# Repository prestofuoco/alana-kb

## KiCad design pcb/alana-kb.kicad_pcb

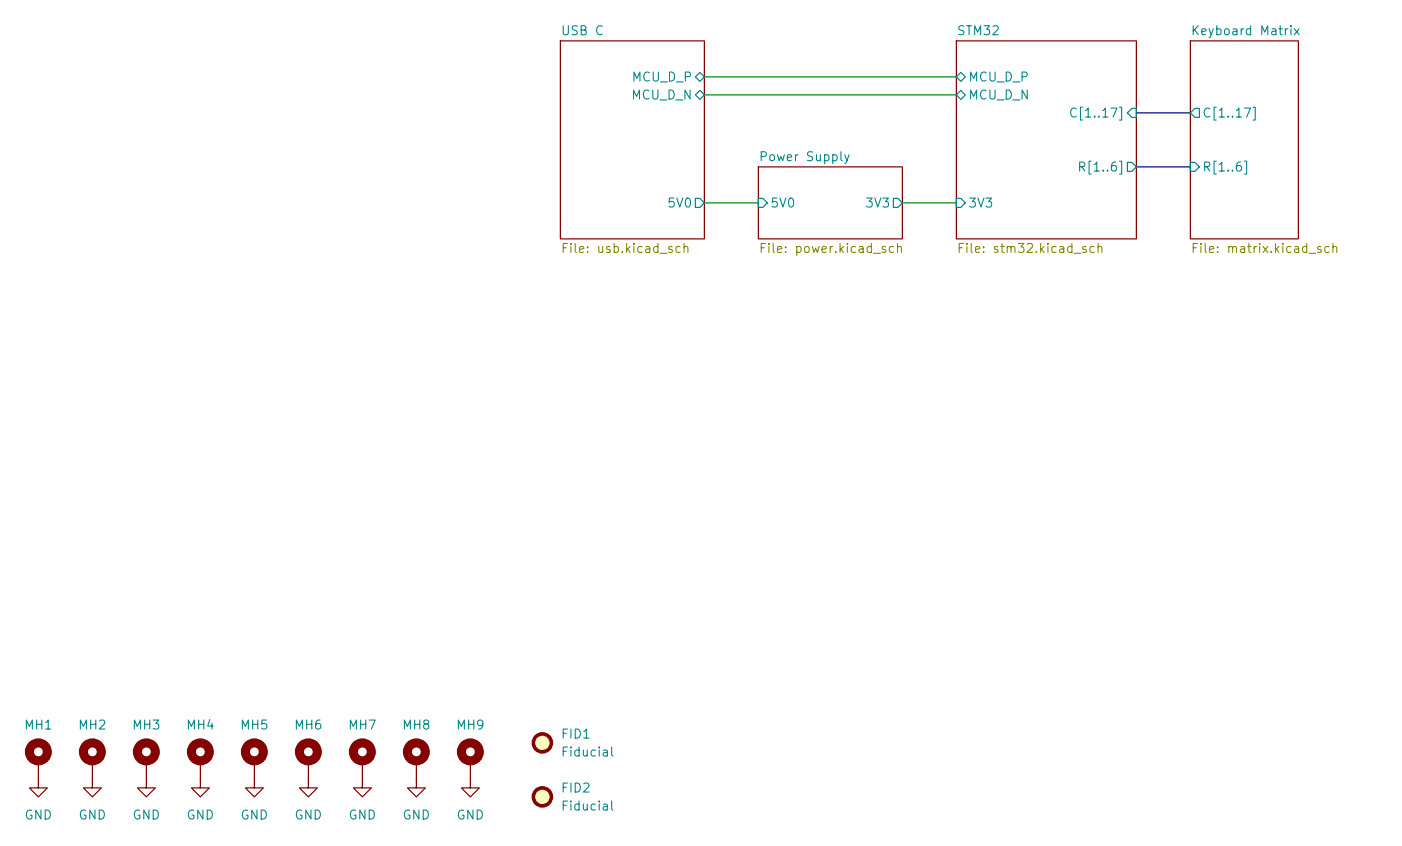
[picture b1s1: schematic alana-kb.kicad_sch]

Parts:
FID1, FID2: Fiducial; Fiducial_1.5mm_Mask4.5mm
MH1, MH2, MH3, MH4, MH5, MH6, MH7, MH8, MH9: MountingHole_Pad; MountingHole_2.2mm_M2_ISO7380_Pad

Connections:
GND: MH1.1, MH2.1, MH3.1, MH4.1, MH5.1, MH6.1, MH7.1, MH8.1, MH9.1; also elsewhere on the board

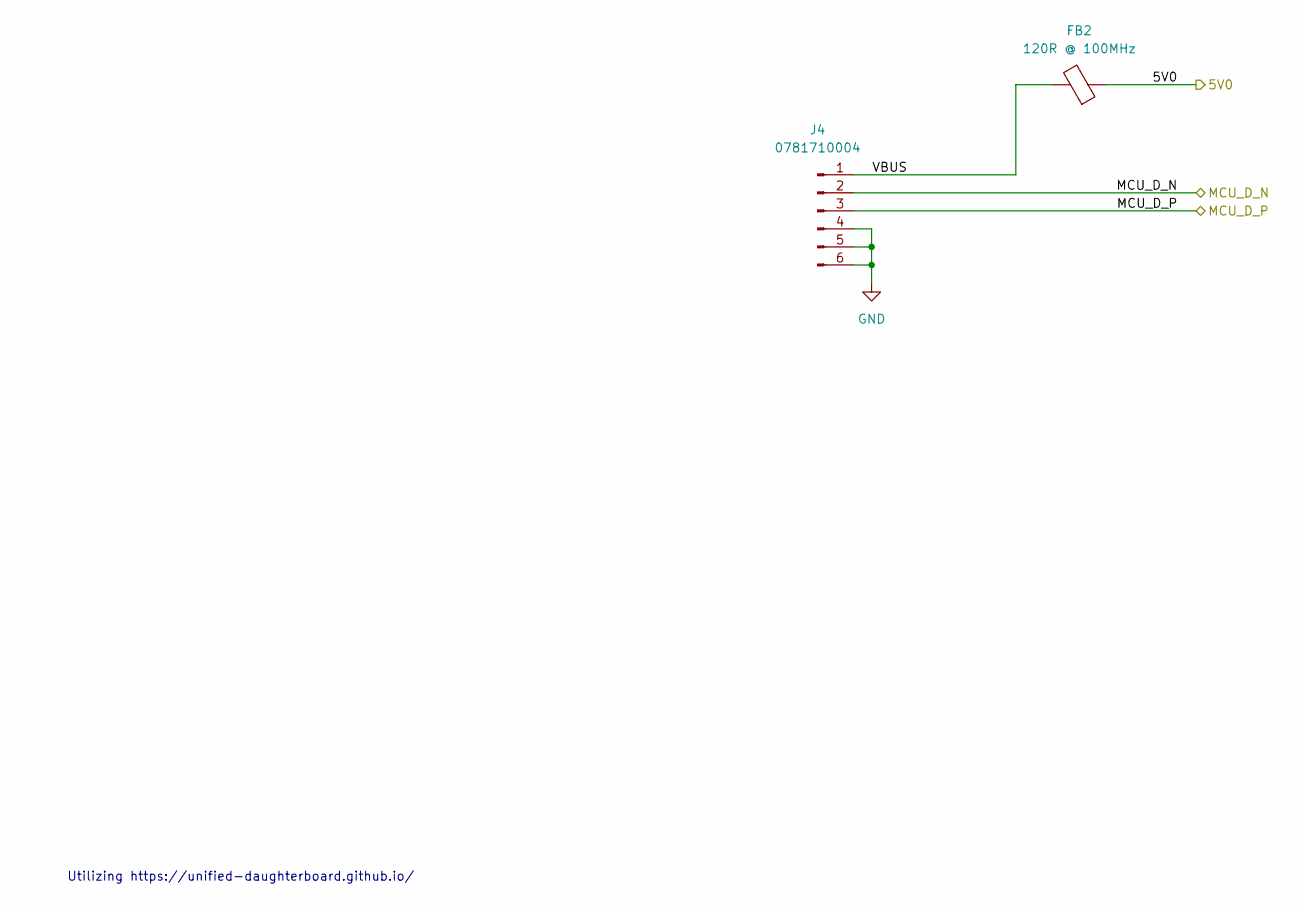
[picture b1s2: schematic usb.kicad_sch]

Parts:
FB2: 120R @ 100MHz; L_0805_2012Metric
J4: 0781710004; CONN_781710000-SD_04_MOL

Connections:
/Power Supply/5V0: FB2.1; also elsewhere on the board
/STM32/MCU_D_N: J4.2; also elsewhere on the board
/STM32/MCU_D_P: J4.3; also elsewhere on the board
/USB C/VBUS: FB2.2, J4.1
GND: J4.4, J4.5, J4.6; also elsewhere on the board

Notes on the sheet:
Utilizing https://unified-daughterboard.github.io/

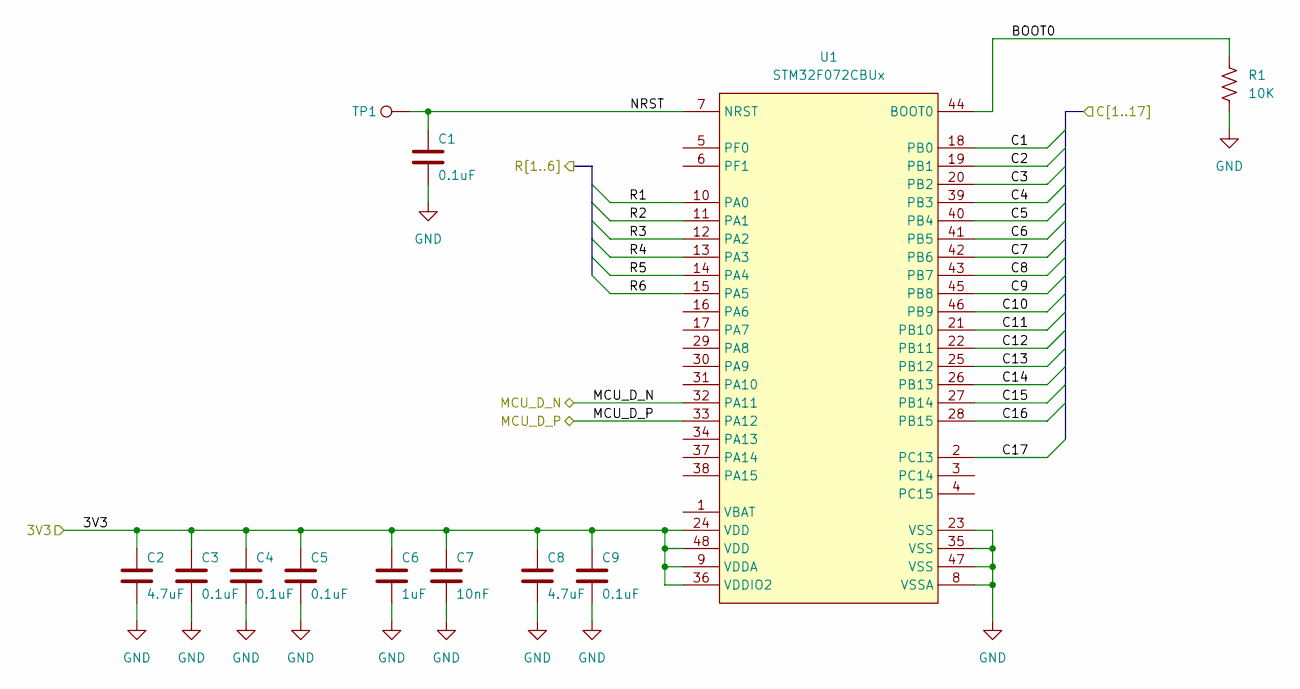
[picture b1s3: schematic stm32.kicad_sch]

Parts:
C1, C3, C4, C5, C9: 0.1uF; C_0402_1005Metric
C2, C8: 4.7uF; C_0603_1608Metric
C6: 1uF; C_0402_1005Metric
C7: 10nF; C_0402_1005Metric
R1: 10K; R_0402_1005Metric
TP1: TestPoint; TestPoint_Pad_D1.0mm
U1: STM32F072CBUx; QFN-48-1EP_7x7mm_P0.5mm_EP5.6x5.6mm

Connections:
/Keyboard Matrix/C1: U1.18 (PB0); also elsewhere on the board
/Keyboard Matrix/C2: U1.19 (PB1); also elsewhere on the board
/Keyboard Matrix/C3: U1.20 (PB2); also elsewhere on the board
/Keyboard Matrix/C4: U1.39 (PB3); also elsewhere on the board
/Keyboard Matrix/C5: U1.40 (PB4); also elsewhere on the board
/Keyboard Matrix/C6: U1.41 (PB5); also elsewhere on the board
/Keyboard Matrix/C7: U1.42 (PB6); also elsewhere on the board
/Keyboard Matrix/C8: U1.43 (PB7); also elsewhere on the board
/Keyboard Matrix/C9: U1.45 (PB8); also elsewhere on the board
/Keyboard Matrix/C10: U1.46 (PB9); also elsewhere on the board
/Keyboard Matrix/C11: U1.21 (PB10); also elsewhere on the board
/Keyboard Matrix/C12: U1.22 (PB11); also elsewhere on the board
/Keyboard Matrix/C13: U1.25 (PB12); also elsewhere on the board
/Keyboard Matrix/C14: U1.26 (PB13); also elsewhere on the board
/Keyboard Matrix/C15: U1.27 (PB14); also elsewhere on the board
/Keyboard Matrix/C16: U1.28 (PB15); also elsewhere on the board
/Keyboard Matrix/C17: U1.2 (PC13); also elsewhere on the board
/Keyboard Matrix/R1: U1.10 (PA0); also elsewhere on the board
/Keyboard Matrix/R2: U1.11 (PA1); also elsewhere on the board
/Keyboard Matrix/R3: U1.12 (PA2); also elsewhere on the board
/Keyboard Matrix/R4: U1.13 (PA3); also elsewhere on the board
/Keyboard Matrix/R5: U1.14 (PA4); also elsewhere on the board
/Keyboard Matrix/R6: U1.15 (PA5); also elsewhere on the board
/Power Supply/3V3: C2.1, C3.1, C4.1, C5.1, C6.1, C7.1, C8.1, C9.1, U1.9 (VDDA), U1.24 (VDD), U1.36 (VDDIO2), U1.48 (VDD); also elsewhere on the board
/STM32/BOOT0: R1.1, U1.44 (BOOT0)
/STM32/MCU_D_N: U1.32 (PA11); also elsewhere on the board
/STM32/MCU_D_P: U1.33 (PA12); also elsewhere on the board
/STM32/NRST: C1.1, TP1.1, U1.7 (NRST)
GND: C1.2, C2.2, C3.2, C4.2, C5.2, C6.2, C7.2, C8.2, C9.2, R1.2, U1.8 (VSSA), U1.23 (VSS), U1.35 (VSS), U1.47 (VSS), U1.49 (GND); also elsewhere on the board

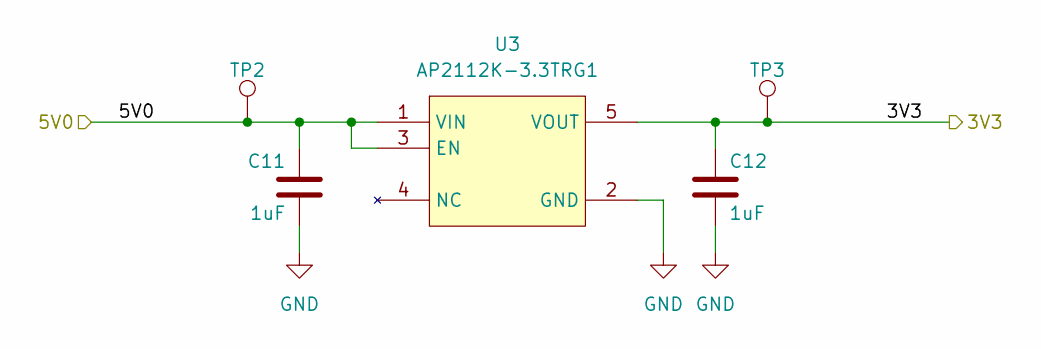
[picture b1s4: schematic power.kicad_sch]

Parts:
C11, C12: 1uF; C_0402_1005Metric
TP2, TP3: TestPoint; TestPoint_Pad_D2.0mm
U3: AP2112K-3.3TRG1; SOT-23-5

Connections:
/Power Supply/3V3: C12.1, TP3.1, U3.5 (VOUT); also elsewhere on the board
/Power Supply/5V0: C11.1, TP2.1, U3.1 (VIN), U3.3 (EN); also elsewhere on the board
GND: C11.2, C12.2, U3.2 (GND); also elsewhere on the board

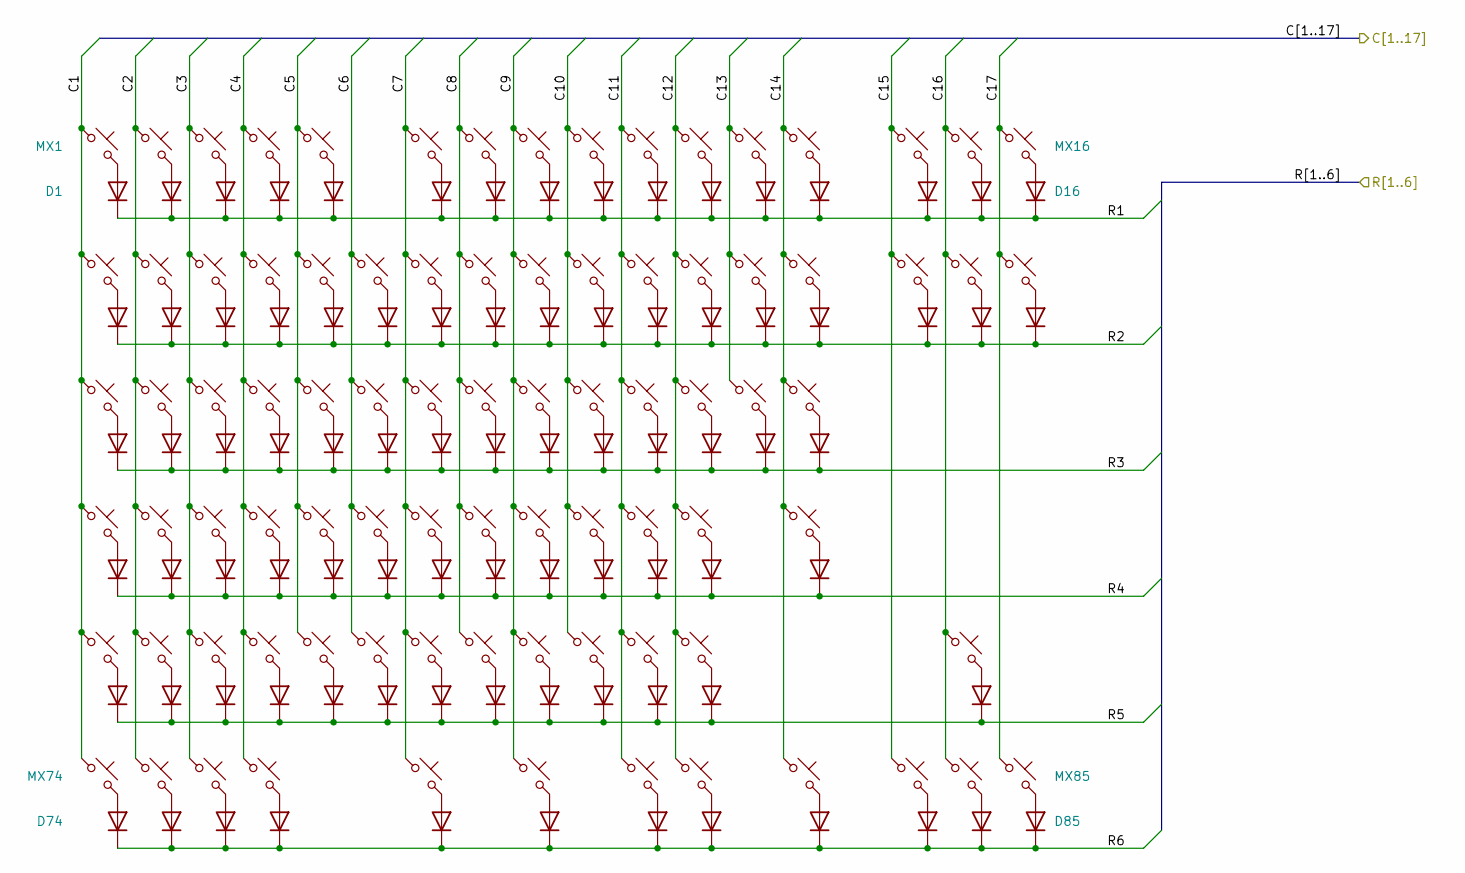
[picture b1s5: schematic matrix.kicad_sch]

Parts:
D1, D2, D3, D4, D5, D6, D7, D8, D9, D10, D11, D12, D13, D14, D15, D16, D17, D18, D19, D20, D21, D22, D23, D24, D25, D26, D27, D28, D29, D30, D31, D32, D33, D34, D35, D36, D37, D38, D39, D40, D41, D42, D43, D44, D45, D46, D47, D48, D49, D50, D51, D52, D53, D54, D55, D56, D57, D58, D59, D60, D61, D62, D63, D64, D65, D66, D67, D68, D69, D70, D71, D72, D73, D74, D75, D76, D77, D78, D79, D80, D81, D82, D83, D84, D85: 1N4148W; D_SOD-123
MX1, MX2, MX3, MX4, MX5, MX6, MX7, MX8, MX9, MX10, MX11, MX12, MX13, MX14, MX15, MX16, MX17, MX18, MX19, MX20, MX21, MX22, MX23, MX24, MX25, MX26, MX27, MX28, MX29, MX30, MX31, MX32, MX33, MX34, MX35, MX36, MX37, MX38, MX39, MX40, MX41, MX42, MX43, MX44, MX45, MX46, MX47, MX48, MX49, MX50, MX51, MX52, MX53, MX54, MX55, MX56, MX57, MX58, MX59, MX60, MX61, MX62, MX63, MX64, MX65, MX66, MX67, MX68, MX69, MX70, MX71, MX72, MX73, MX74, MX75, MX76, MX77, MX78, MX79, MX80, MX81, MX82, MX83, MX84, MX85: MX_SW_solder; SW_MX_1u

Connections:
/Keyboard Matrix/C1: MX1.1, MX17.1, MX34.1, MX48.1, MX61.1, MX74.1; also elsewhere on the board
/Keyboard Matrix/C2: MX2.1, MX18.1, MX35.1, MX49.1, MX62.1, MX75.1; also elsewhere on the board
/Keyboard Matrix/C3: MX3.1, MX19.1, MX36.1, MX50.1, MX63.1, MX76.1; also elsewhere on the board
/Keyboard Matrix/C4: MX4.1, MX20.1, MX37.1, MX51.1, MX64.1, MX77.1; also elsewhere on the board
/Keyboard Matrix/C5: MX5.1, MX21.1, MX38.1, MX52.1, MX65.1; also elsewhere on the board
/Keyboard Matrix/C6: MX22.1, MX39.1, MX53.1, MX66.1; also elsewhere on the board
/Keyboard Matrix/C7: MX6.1, MX23.1, MX40.1, MX54.1, MX67.1, MX78.1; also elsewhere on the board
/Keyboard Matrix/C8: MX7.1, MX24.1, MX41.1, MX55.1, MX68.1; also elsewhere on the board
/Keyboard Matrix/C9: MX8.1, MX25.1, MX42.1, MX56.1, MX69.1, MX79.1; also elsewhere on the board
/Keyboard Matrix/C10: MX9.1, MX26.1, MX43.1, MX57.1, MX70.1; also elsewhere on the board
/Keyboard Matrix/C11: MX10.1, MX27.1, MX44.1, MX58.1, MX71.1, MX80.1; also elsewhere on the board
/Keyboard Matrix/C12: MX11.1, MX28.1, MX45.1, MX59.1, MX72.1, MX81.1; also elsewhere on the board
/Keyboard Matrix/C13: MX12.1, MX29.1, MX46.1; also elsewhere on the board
/Keyboard Matrix/C14: MX13.1, MX30.1, MX47.1, MX60.1, MX82.1; also elsewhere on the board
/Keyboard Matrix/C15: MX14.1, MX31.1, MX83.1; also elsewhere on the board
/Keyboard Matrix/C16: MX15.1, MX32.1, MX73.1, MX84.1; also elsewhere on the board
/Keyboard Matrix/C17: MX16.1, MX33.1, MX85.1; also elsewhere on the board
/Keyboard Matrix/R1: D1.1 (K), D2.1 (K), D3.1 (K), D4.1 (K), D5.1 (K), D6.1 (K), D7.1 (K), D8.1 (K), D9.1 (K), D10.1 (K), D11.1 (K), D12.1 (K), D13.1 (K), D14.1 (K), D15.1 (K), D16.1 (K); also elsewhere on the board
/Keyboard Matrix/R2: D17.1 (K), D18.1 (K), D19.1 (K), D20.1 (K), D21.1 (K), D22.1 (K), D23.1 (K), D24.1 (K), D25.1 (K), D26.1 (K), D27.1 (K), D28.1 (K), D29.1 (K), D30.1 (K), D31.1 (K), D32.1 (K), D33.1 (K); also elsewhere on the board
/Keyboard Matrix/R3: D34.1 (K), D35.1 (K), D36.1 (K), D37.1 (K), D38.1 (K), D39.1 (K), D40.1 (K), D41.1 (K), D42.1 (K), D43.1 (K), D44.1 (K), D45.1 (K), D46.1 (K), D47.1 (K); also elsewhere on the board
/Keyboard Matrix/R4: D48.1 (K), D49.1 (K), D50.1 (K), D51.1 (K), D52.1 (K), D53.1 (K), D54.1 (K), D55.1 (K), D56.1 (K), D57.1 (K), D58.1 (K), D59.1 (K), D60.1 (K); also elsewhere on the board
/Keyboard Matrix/R5: D61.1 (K), D62.1 (K), D63.1 (K), D64.1 (K), D65.1 (K), D66.1 (K), D67.1 (K), D68.1 (K), D69.1 (K), D70.1 (K), D71.1 (K), D72.1 (K), D73.1 (K); also elsewhere on the board
/Keyboard Matrix/R6: D74.1 (K), D75.1 (K), D76.1 (K), D77.1 (K), D78.1 (K), D79.1 (K), D80.1 (K), D81.1 (K), D82.1 (K), D83.1 (K), D84.1 (K), D85.1 (K); also elsewhere on the board
unnamed: D1.2 (A), MX1.2
unnamed: D2.2 (A), MX2.2
unnamed: D3.2 (A), MX3.2
unnamed: D4.2 (A), MX4.2
unnamed: D5.2 (A), MX5.2
unnamed: D6.2 (A), MX6.2
unnamed: D7.2 (A), MX7.2
unnamed: D8.2 (A), MX8.2
unnamed: D9.2 (A), MX9.2
unnamed: D10.2 (A), MX10.2
unnamed: D11.2 (A), MX11.2
unnamed: D12.2 (A), MX12.2
unnamed: D13.2 (A), MX13.2
unnamed: D14.2 (A), MX14.2
unnamed: D15.2 (A), MX15.2
unnamed: D16.2 (A), MX16.2
unnamed: D17.2 (A), MX17.2
unnamed: D18.2 (A), MX18.2
unnamed: D19.2 (A), MX19.2
unnamed: D20.2 (A), MX20.2
unnamed: D21.2 (A), MX21.2
unnamed: D22.2 (A), MX22.2
unnamed: D23.2 (A), MX23.2
unnamed: D24.2 (A), MX24.2
unnamed: D25.2 (A), MX25.2
unnamed: D26.2 (A), MX26.2
unnamed: D27.2 (A), MX27.2
unnamed: D28.2 (A), MX28.2
unnamed: D29.2 (A), MX29.2
unnamed: D30.2 (A), MX30.2
unnamed: D31.2 (A), MX31.2
unnamed: D32.2 (A), MX32.2
unnamed: D33.2 (A), MX33.2
unnamed: D34.2 (A), MX34.2
unnamed: D35.2 (A), MX35.2
unnamed: D36.2 (A), MX36.2
unnamed: D37.2 (A), MX37.2
unnamed: D38.2 (A), MX38.2
unnamed: D39.2 (A), MX39.2
unnamed: D40.2 (A), MX40.2
unnamed: D41.2 (A), MX41.2
unnamed: D42.2 (A), MX42.2
unnamed: D43.2 (A), MX43.2
unnamed: D44.2 (A), MX44.2
unnamed: D45.2 (A), MX45.2
unnamed: D46.2 (A), MX46.2
unnamed: D47.2 (A), MX47.2
unnamed: D48.2 (A), MX48.2
unnamed: D49.2 (A), MX49.2
unnamed: D50.2 (A), MX50.2
unnamed: D51.2 (A), MX51.2
unnamed: D52.2 (A), MX52.2
unnamed: D53.2 (A), MX53.2
unnamed: D54.2 (A), MX54.2
unnamed: D55.2 (A), MX55.2
unnamed: D56.2 (A), MX56.2
unnamed: D57.2 (A), MX57.2
unnamed: D58.2 (A), MX58.2
unnamed: D59.2 (A), MX59.2
unnamed: D60.2 (A), MX60.2
unnamed: D61.2 (A), MX61.2
unnamed: D62.2 (A), MX62.2
unnamed: D63.2 (A), MX63.2
unnamed: D64.2 (A), MX64.2
unnamed: D65.2 (A), MX65.2
unnamed: D66.2 (A), MX66.2
unnamed: D67.2 (A), MX67.2
unnamed: D68.2 (A), MX68.2
unnamed: D69.2 (A), MX69.2
unnamed: D70.2 (A), MX70.2
unnamed: D71.2 (A), MX71.2
unnamed: D72.2 (A), MX72.2
unnamed: D73.2 (A), MX73.2
unnamed: D74.2 (A), MX74.2
unnamed: D75.2 (A), MX75.2
unnamed: D76.2 (A), MX76.2
unnamed: D77.2 (A), MX77.2
unnamed: D78.2 (A), MX78.2
unnamed: D79.2 (A), MX79.2
unnamed: D80.2 (A), MX80.2
unnamed: D81.2 (A), MX81.2
unnamed: D82.2 (A), MX82.2
unnamed: D83.2 (A), MX83.2
unnamed: D84.2 (A), MX84.2
unnamed: D85.2 (A), MX85.2

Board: 2 copper layers, 200 parts (104 on the bottom side), 116 nets, no tracks yet.

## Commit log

2026-01-11 initial firmware structure commit
2026-01-11 usb c, power, mcu
2026-01-11 cleanup, add kb matrix
2026-01-11 removed bin
2026-01-11 kb matrix complete, stm32 wiring done
2026-01-11 replaced usb c with molex for udb
2026-01-12 reroute matrix
2026-01-14 finish layout
2026-01-14 bom fb part, complete
2026-02-08 firmware layout definition
2026-02-08 cleaned unused dirs
2026-02-24 fixed keymap
2026-02-25 added firmware build workflow
2026-02-25 updated ci/cd
2026-02-25 removed pcb history dir
2026-02-25 Triggering build
2026-02-25 edited ci/cd
2026-02-25 added dfu-util to workflow
2026-02-25 updated qmk compile
2026-02-25 fix firmware build
